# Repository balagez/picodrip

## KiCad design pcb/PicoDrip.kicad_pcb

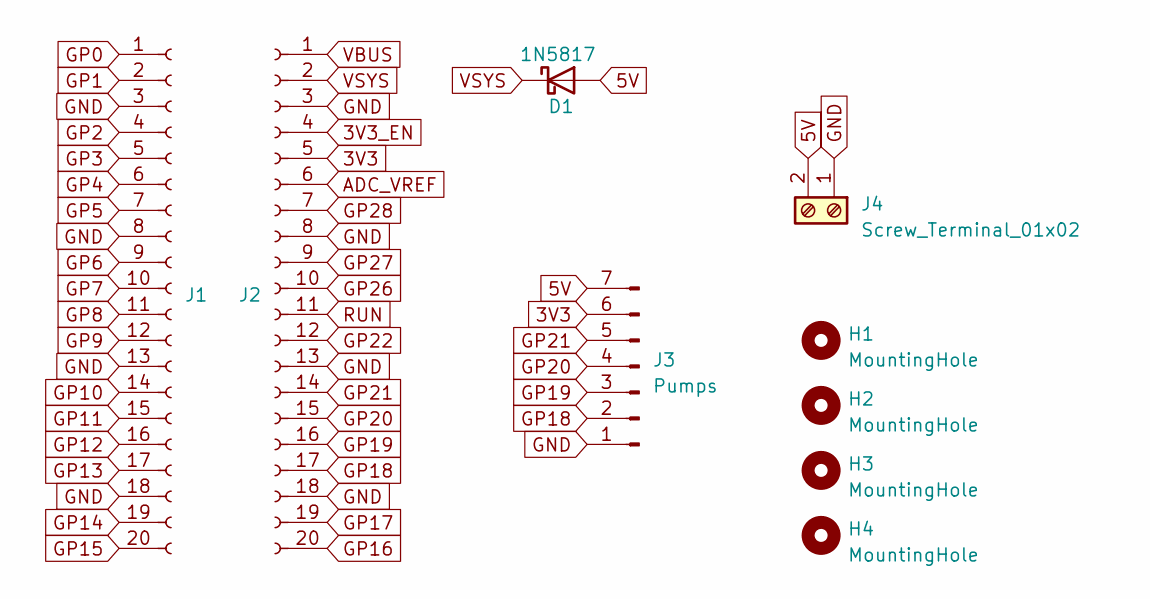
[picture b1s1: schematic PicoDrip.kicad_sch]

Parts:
D1: 1N5817; D_DO-41_SOD81_P10.16mm_Horizontal
H1, H2, H3, H4: MountingHole; MountingHole_2.1mm
J1, J2: Conn_01x20_Socket; PinSocket_1x20_P2.54mm_Vertical
J3: Pumps; PinHeader_1x07_P2.54mm_Vertical
J4: Screw_Terminal_01x02; TerminalBlock_Phoenix_MKDS-1,5-2-5.08_1x02_P5.08mm_Horizont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

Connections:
3V3: J2.5, J3.6
3V3_EN: J2.4
5V: D1.2 (A), J3.7, J4.2
ADC_VREF: J2.6
GND: J1.3, J1.8, J1.13, J1.18, J2.3, J2.8, J2.13, J2.18, J3.1, J4.1
GP0: J1.1
GP1: J1.2
GP2: J1.4
GP3: J1.5
GP4: J1.6
GP5: J1.7
GP6: J1.9
GP7: J1.10
GP8: J1.11
GP9: J1.12
GP10: J1.14
GP11: J1.15
GP12: J1.16
GP13: J1.17
GP14: J1.19
GP15: J1.20
GP16: J2.20
GP17: J2.19
GP18: J2.17, J3.2
GP19: J2.16, J3.3
GP20: J2.15, J3.4
GP21: J2.14, J3.5
GP22: J2.12
GP26: J2.10
GP27: J2.9
GP28: J2.7
RUN: J2.11
VBUS: J2.1
VSYS: D1.1 (K), J2.2

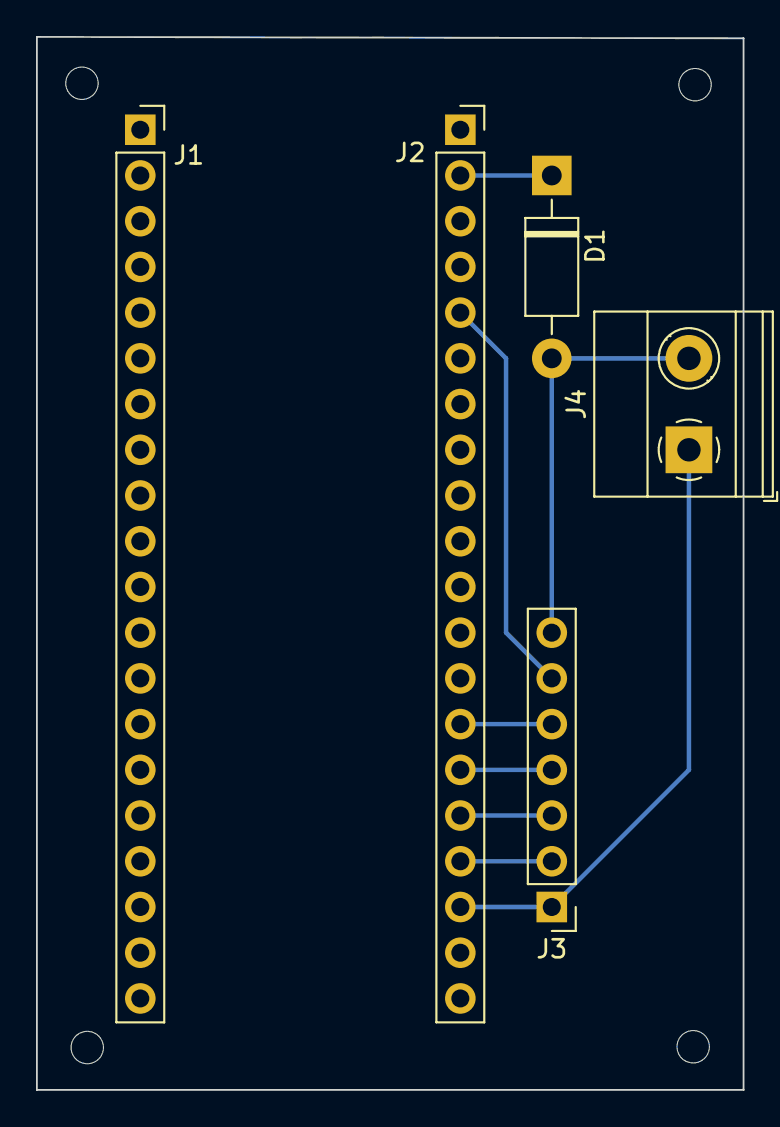
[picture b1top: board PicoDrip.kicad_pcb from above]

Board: 2 copper layers, 39.3 x 58.5 mm, 9 parts (0 on the bottom side), 8 nets.

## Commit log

2023-05-14 Fixes
2023-05-16 Fix timestamps and timer, add logrotate
2023-05-16 Add PCB design
2023-05-24 Update simulator
2023-05-24 Time zone fixes
